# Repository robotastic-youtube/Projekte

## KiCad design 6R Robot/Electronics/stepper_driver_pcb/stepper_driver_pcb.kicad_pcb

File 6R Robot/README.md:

# Robotastic 6R-Robot & FOC Controller

This repository contains all the necessary resources for building and controlling a 6-axis robotic arm (6R-Robot), along with the custom electronics and firmware. The project relies on a hardware abstraction layer and Field-Oriented Control (FOC) for precise stepper motor operation.

## ⚠️ IMPORTANT SAFETY WARNING & DISCLAIMER ⚠️

This project involves building and operating a **6-axis robot** driven by stepper motors and custom electronics. Please strictly observe the following points before attempting to build or operate it:

* **Mechanical Hazard:** A robotic arm can move unpredictably, at high speeds, and with significant force—especially during programming, FOC parameter tuning, or due to unforeseen software bugs. Always maintain a safe distance during operation and **never** reach into the robot's workspace while it is powered on!
* **Electrical Hazard:** This system operates with voltages and high-current power supplies (e.g., 24V) that can cause fires, severe injuries, or the destruction of hardware if wired incorrectly, short-circuited, or overloaded. Adequate foundational knowledge of electronics is strictly required.
* **Not an Industrial Product:** This is an experimental DIY and educational project. It does not carry a CE mark and lacks the certified safety mechanisms (such as verified emergency stop chains or light curtains) found in commercial industrial robots.

**Use at Your Own Risk:**
Building, programming, and operating this robot is done **entirely at your own risk**. The author (Robotastic) assumes absolutely no liability for any personal injury, property damage, or financial loss resulting from the construction, use, or potential malfunction of this project.

## 1. Folder Structure

The project is organized into three main directories:

* **`Electronics/`**: Contains the **KiCad files** for the custom FOC PCB designed to drive the stepper motors.
* **`Code/`**: Contains the **Firmware** for the PCBs. This code is built using PlatformIO and implements hardware initialization, CAN-bus communication, and the FOC algorithm.
* **`3D-Files/`**: Contains the mechanical designs in **STEP format**.
    * Individual joints are provided as assemblies named `Joint1` through `Joint6`.
    * The file `6R-Robot Assembly` contains the complete, assembled robot model.

## 2. Documentation & Build Guide

For detailed videos on how to assemble the robot, explanations of the electronics, and the software, please visit the **Robotastic YouTube Channel**:

👉 [Robotastic YouTube Channel](https://www.youtube.com/channel/UCKuV_Eh0zMl3OSophDiDIqA)

## 3. Current Project Status (Hardware)

Please note that this project is currently a **Work in Progress (WIP)**.
* There is currently **no official Bill of Materials (BOM)** or detailed guide available.
* However, the robot can still be built, as the necessary components can be inferred from the provided documentation, PCB designs, and 3D models.

## 4. Software Status

The firmware provided in the `Code/` folder is designed for the direct low-level control of the motor drivers:
* **Currently Implemented**: Low-level drivers, FOC logic, CAN communication, and simple motion commands (Position, Velocity, Torque, Trajectory points).
* **Not Yet Implemented**: There is currently **no high-level software** for path planning (such as Inverse Kinematics or full-arm trajectory generation) or a graphical user interface (GUI) to control the robot as a complete system.

## 5. Getting Started (PlatformIO)

This project is built using **PlatformIO**, which is the recommended development environment.

### How to load the project:
1. **Install VS Code:** Download and install Visual Studio Code.
2. **Install PlatformIO:** Search for the "PlatformIO IDE" extension in the VS Code marketplace and install it.
3. **Open Project:**
   - Clone this repository or download the source code.
   - In PlatformIO Home, click on "Open Project" and select the folder containing `platformio.ini`.
4. **Build & Upload:**
   - Connect your STM32 board via USB (ensure you have the correct programmer, e.g., ST-Link).
   - Use the PlatformIO toolbar (bottom bar) to click the **Build** (Checkmark) and then **Upload** (Arrow) icons.

## License

This software, hardware design, and mechanical design are provided for **educational and personal use only**. 
**Commercial use is strictly prohibited** without prior written permission from the author. 

Please see the `LICENSE` file for the complete Robotastic Non-Commercial License terms.

*This project relies on the excellent SimpleFOC library, which is licensed under the MIT License.*

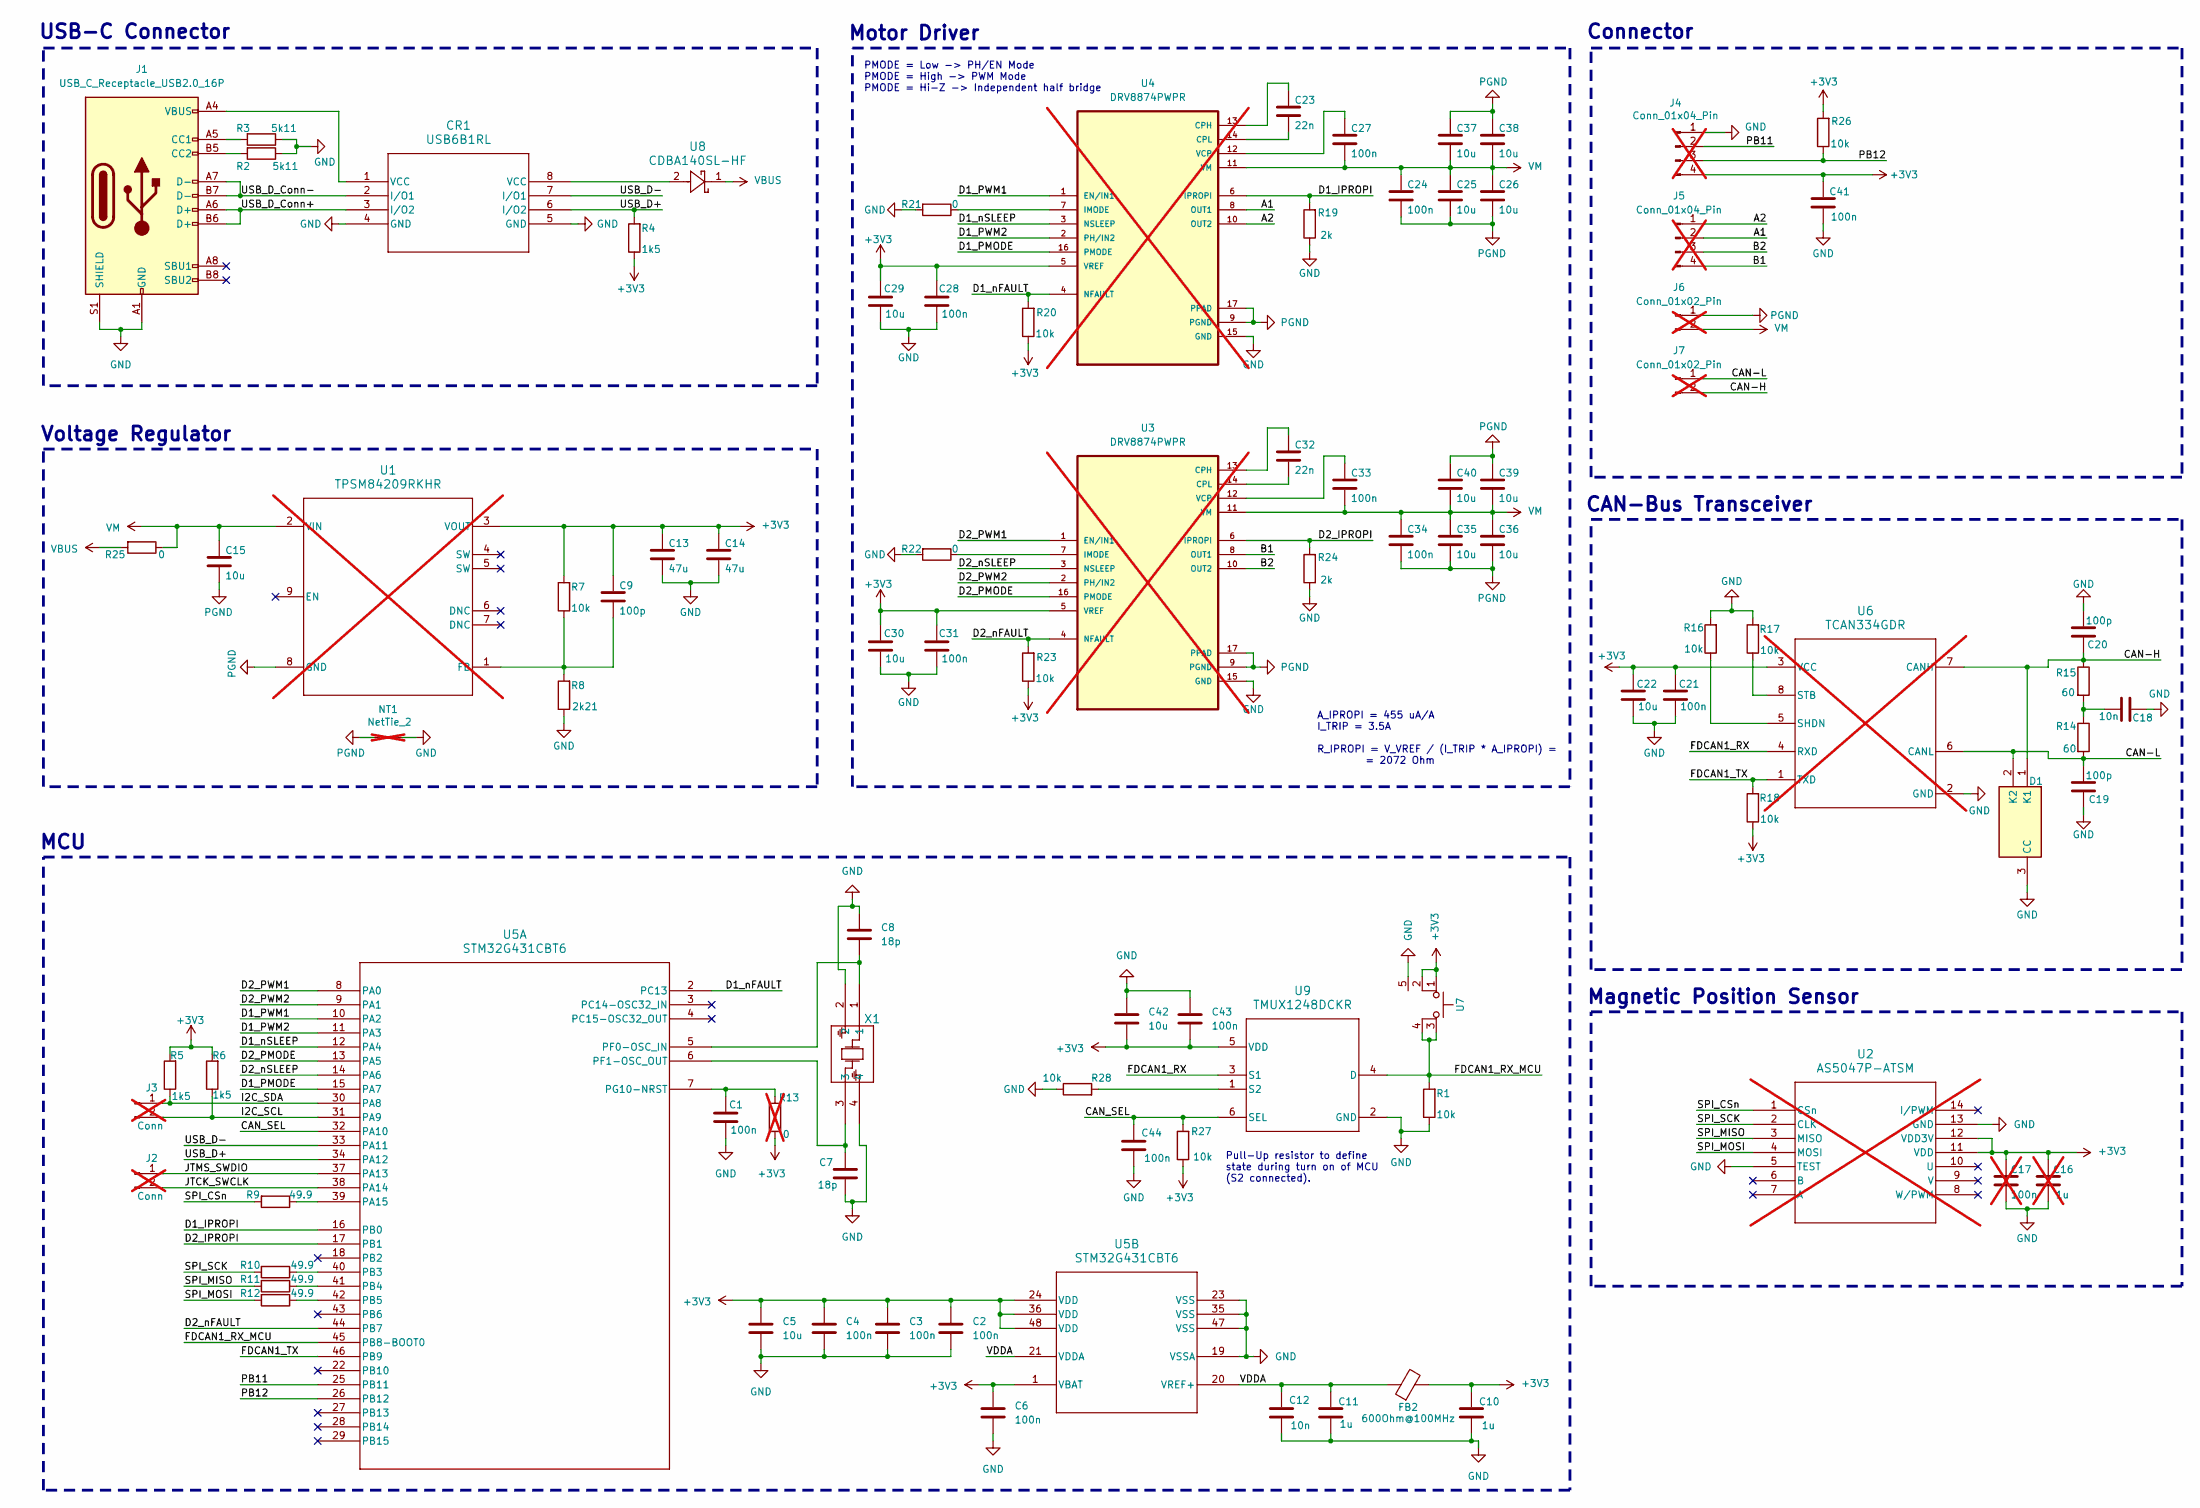
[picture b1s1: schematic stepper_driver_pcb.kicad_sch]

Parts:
C1, C2, C3, C4, C6, C21, C24, C27, C28, C31, C33, C34, C41, C43, C44: 100n; C_0603_1608Metric; LCSC C14663
C5, C22, C29, C30, C42: 10u; C_0603_1608Metric; LCSC C19702
C7, C8: 18p; C_0603_1608Metric; LCSC C1647
C9, C19, C20: 100p; C_0603_1608Metric; LCSC C14858
C10, C11: 1u; C_0603_1608Metric; LCSC C15849
C12, C18: 10n; C_0603_1608Metric; LCSC C57112
C13, C14: 47u; C_0805_2012Metric; LCSC C16780
C15: 10u; C_0805_2012Metric; LCSC C440198
C16: 1u; C_0603_1608Metric; LCSC C15849; not fitted
C17: 100n; C_0603_1608Metric; LCSC C14663; not fitted
C23, C32: 22n; C_0603_1608Metric; LCSC C21122
C25, C26, C35, C36, C37, C38, C39, C40: 10u; C_1206_3216Metric; LCSC C13585
CR1: USB6B1RL; SO-8_STM; LCSC C7419953
D1: PESD2CANFD24L-UX; SOT65P210X110-3N; Mouser Part Number 771-PESD2CANFD24L-UX
FB2: 600Ohm@100MHz; R_0603_1608Metric; LCSC C1002
J1: USB_C_Receptacle_USB2.0_16P; USB_C_Receptacle_G-Switch_GT-USB-7010ASV; LCSC C2988369
J2, J3: Conn; PinHeader_1x02_P2.54mm_Vertical; not fitted
J4: Conn_01x04_Pin; PinHeader_1x04_P2.54mm_Vertical; not fitted
J5: Conn_01x04_Pin; JST_XH_B4B-XH-AM_1x04_P2.50mm_Vertical; LCSC C5368777; not fitted
J6, J7: Conn_01x02_Pin; TerminalBlock_4Ucon_1x02_P3.50mm_Horizontal; not fitted
NT1: NetTie_2; NetTie-2_THT_Pad0.3mm; not fitted
R1, R7, R16, R17, R18, R20, R23, R26, R27, R28: 10k; R_0603_1608Metric; LCSC C25804
R2, R3: 5k11; R_0603_1608Metric; LCSC C23186
R4, R5, R6: 1k5; R_0603_1608Metric; LCSC C22843
R8: 2k21; R_0603_1608Metric; LCSC C4190
R9, R10, R11, R12: 49.9; R_0603_1608Metric; LCSC C23185
R13: 0; R_0603_1608Metric; LCSC C21189; not fitted
R14, R15: 60; R_0603_1608Metric; LCSC C2933247
R19, R24: 2k; R_0603_1608Metric; LCSC C22975
R21, R22, R25: 0; R_0603_1608Metric; LCSC C21189
U1: TPSM84209RKHR; RKH0009A; LCSC C2878926; not fitted
U2: AS5047P-ATSM; TSSOP14_OSM; LCSC C962063; not fitted
U3, U4: DRV8874PWPR; SOP65P640X120-17N; LCSC C1855818; not fitted
U5: STM32G431CBT6; LQFP48-7x7mm; LCSC C529355
U6: TCAN334GDR; D0008A_L; LCSC C189939; not fitted
U7: YTS-A007; LCSC C967770
U8: CDBA140SL-HF; CDBA-HF; LCSC C3012747
U9: TMUX1248DCKR; DCK0006A-IPC_C; LCSC C3656915
X1: ABM3B-8.000MHZ-B2-T; ABM3B_ABR; LCSC C83312

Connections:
+3V3: C2.1, C3.1, C4.1, C5.1, C6.1, C9.1, C10.1, C13.1, C14.1, C16.1, C17.1, C21.1, C22.1, C28.1, C29.1, C30.1, C31.1, C41.1, C42.2, C43.2, FB2.2, J4.4, R4.1, R5.2, R6.2, R7.2, R13.2, R18.1, R20.1, R23.1, R26.2, R27.1, U1.3 (VOUT), U2.11 (VDD), U2.12 (VDD3V), U3.5 (VREF), U4.5 (VREF), U5.1 (VBAT), U5.24 (VDD), U5.36 (VDD), U5.48 (VDD), U6.3 (VCC), U7.1, U7.2, U9.5 (VDD)
/A1: J5.2, U4.8 (OUT1)
/A2: J5.1, U4.10 (OUT2)
/B1: J5.4, U3.8 (OUT1)
/B2: J5.3, U3.10 (OUT2)
/CAN-H: C20.1, D1.1 (K1), J7.2, R15.1, U6.7 (CANH)
/CAN-L: C19.1, D1.2 (K2), J7.1, R14.2, U6.6 (CANL)
/CAN_SEL: C44.2, R27.2, U5.32 (PA10), U9.6 (SEL)
/D1_IPROPI: R19.2, U4.6 (IPROPI), U5.16 (PB0)
/D1_PMODE: U4.16 (PMODE), U5.15 (PA7)
/D1_PWM1: U4.1 (EN/IN1), U5.10 (PA2)
/D1_PWM2: U4.2 (PH/IN2), U5.11 (PA3)
/D1_nFAULT: R20.2, U4.4 (NFAULT), U5.2 (PC13)
/D1_nSLEEP: U4.3 (NSLEEP), U5.12 (PA4)
/D2_IPROPI: R24.2, U3.6 (IPROPI), U5.17 (PB1)
/D2_PMODE: U3.16 (PMODE), U5.13 (PA5)
/D2_PWM1: U3.1 (EN/IN1), U5.8 (PA0)
/D2_PWM2: U3.2 (PH/IN2), U5.9 (PA1)
/D2_nFAULT: R23.2, U3.4 (NFAULT), U5.44 (PB7)
/D2_nSLEEP: U3.3 (NSLEEP), U5.14 (PA6)
/FDCAN1_RX: U6.4 (RXD), U9.3 (S1)
/FDCAN1_RX_MCU: R1.2, U5.45 (PB8-BOOT0), U7.3, U7.4, U9.4 (D)
/FDCAN1_TX: R18.2, U5.46 (PB9), U6.1 (TXD)
/I2C_SCL: J3.2, R6.1, U5.31 (PA9)
/I2C_SDA: J3.1, R5.1, U5.30 (PA8)
/JTCK_SWCLK: J2.2, U5.38 (PA14)
/JTMS_SWDIO: J2.1, U5.37 (PA13)
/PB11: J4.2, U5.25 (PB11)
/PB12: J4.3, R26.1, U5.26 (PB12)
/SPI_CSn: R9.2, U2.1 (CSn)
/SPI_MISO: R11.2, U2.3 (MISO)
/SPI_MOSI: R12.2, U2.4 (MOSI)
/SPI_SCK: R10.2, U2.2 (CLK)
/USB_D+: CR1.6 (I/O2), R4.2, U5.34 (PA12)
/USB_D-: CR1.7 (I/O1), U5.33 (PA11)
/USB_D_Conn+: CR1.3 (I/O2), J1.A6 (D+), J1.B6 (D+)
/USB_D_Conn-: CR1.2 (I/O1), J1.A7 (D-), J1.B7 (D-)
/VDDA: C11.1, C12.1, FB2.1, U5.20 (VREF+), U5.21 (VDDA)
GND: C1.2, C2.2, C3.2, C4.2, C5.2, C6.2, C7.2, C8.1, C10.2, C11.2, C12.2, C13.2, C14.2, C16.2, C17.2, C18.1, C19.2, C20.2, C21.2, C22.2, C28.2, C29.2, C30.2, C31.2, C41.2, C42.1, C43.1, C44.1, CR1.4 (GND), CR1.5 (GND), D1.3 (CC), J1.A1 (GND), J1.A12 (GND), J1.B1 (GND), J1.B12 (GND), J1.S1 (SHIELD), J4.1, NT1.2, R1.1, R2.1, R3.1, R8.1, R16.2, R17.2, R19.1, R21.2, R22.2, R24.1, R28.1, U2.5 (TEST), U2.13 (GND), U3.15 (GND), U4.15 (GND), U5.19 (VSSA), U5.23 (VSS), U5.35 (VSS), U5.47 (VSS), U6.2 (GND), U7.5, U9.2 (GND), X1.2, X1.4
unnamed: C18.2, R14.1, R15.2
unnamed: CR1.1 (VCC), J1.A4 (VBUS), J1.A9 (VBUS), J1.B4 (VBUS), J1.B9 (VBUS)
unnamed: CR1.8 (VCC), U8.2
unnamed: J1.A5 (CC1), R3.2
unnamed: J1.B5 (CC2), R2.2
unnamed: C9.2, R7.1, R8.2, U1.1 (FB)
unnamed: C32.1, U3.13 (CPH)
unnamed: C32.2, U3.14 (CPL)
unnamed: R22.1, U3.7 (IMODE)
unnamed: C33.1, U3.12 (VCP)
unnamed: C23.1, U4.13 (CPH)
unnamed: C23.2, U4.14 (CPL)
unnamed: R21.1, U4.7 (IMODE)
unnamed: C27.1, U4.12 (VCP)
unnamed: R9.1, U5.39 (PA15)
unnamed: R10.1, U5.40 (PB3)
unnamed: R11.1, U5.41 (PB4)
unnamed: R12.1, U5.42 (PB5)
unnamed: C8.2, U5.5 (PF0-OSC_IN), X1.1
unnamed: C7.1, U5.6 (PF1-OSC_OUT), X1.3
unnamed: C1.1, R13.1, U5.7 (PG10-NRST)
unnamed: R16.1, U6.5 (SHDN)
unnamed: R17.1, U6.8 (STB)
unnamed: R28.2, U9.1 (S2)
PGND: C15.2, C24.2, C25.2, C26.2, C34.2, C35.2, C36.2, C37.1, C38.1, C39.1, C40.1, J6.1, NT1.1, U1.8 (GND), U3.9 (PGND), U3.17 (PPAD), U4.9 (PGND), U4.17 (PPAD)
VBUS: R25.2, U8.1
VM: C15.1, C24.1, C25.1, C26.1, C27.2, C33.2, C34.1, C35.1, C36.1, C37.2, C38.2, C39.2, C40.2, J6.2, R25.1, U1.2 (VIN), U3.11 (VM), U4.11 (VM)

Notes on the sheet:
PMODE = Low -> PH/EN Mode PMODE = High -> PWM Mode PMODE = Hi-Z -> Independent half bridge
MCU
Magnetic Position Sensor
Connector
A_IPROPI = 455 uA/A I_TRIP = 3.5A R_IPROPI = V_VREF / (I_TRIP * A_IPROPI) = = 2072 Ohm
USB-C Connector
CAN-Bus Transceiver
Pull-Up resistor to define state during turn on of MCU (S2 connected).
Motor Driver
Voltage Regulator

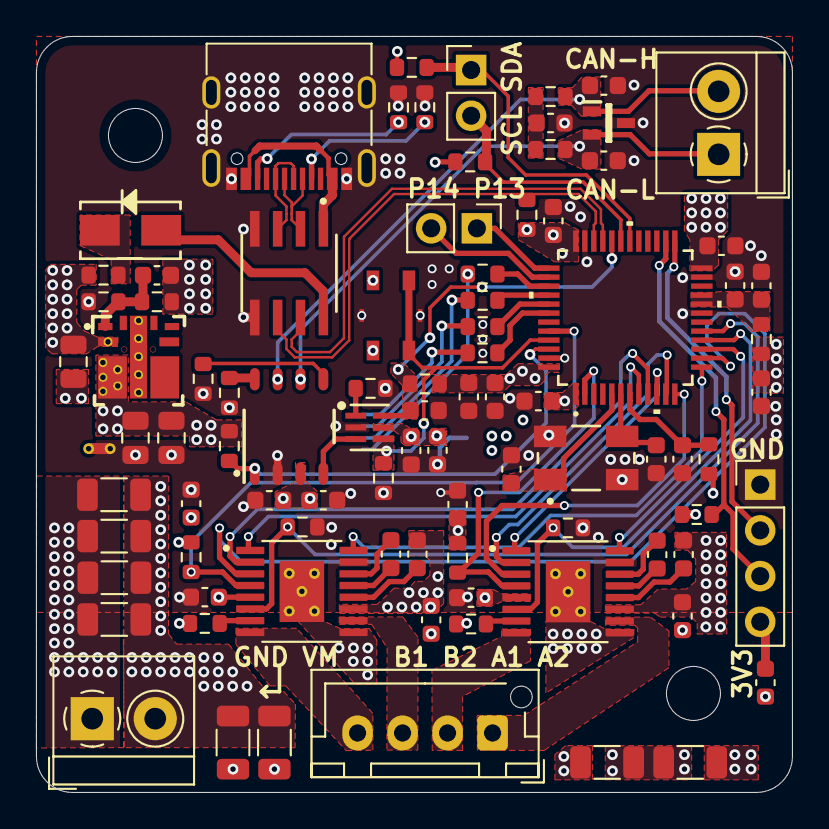
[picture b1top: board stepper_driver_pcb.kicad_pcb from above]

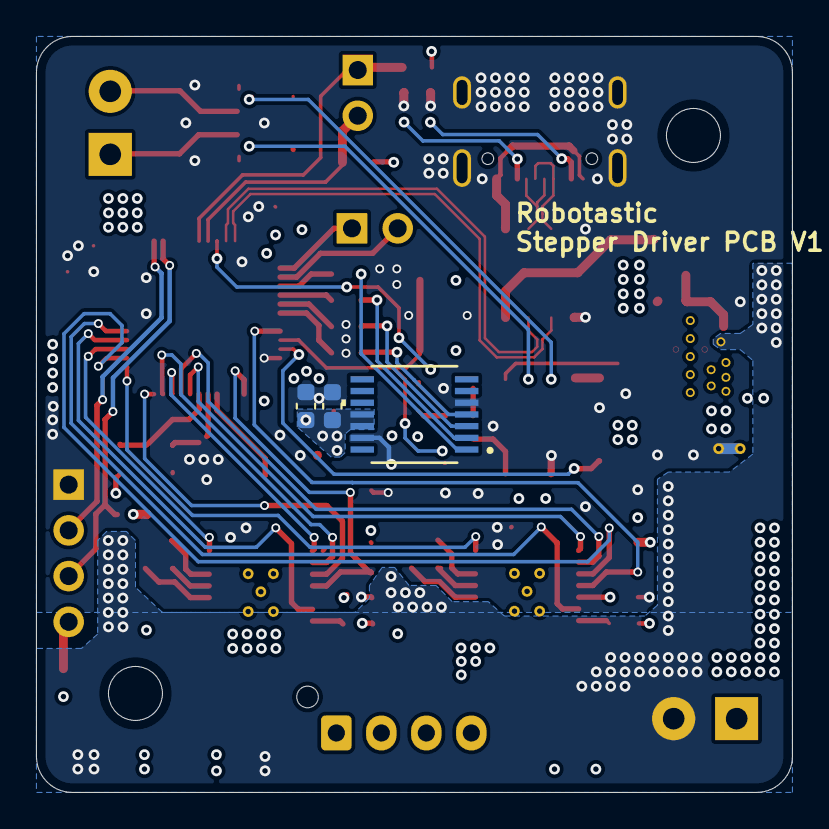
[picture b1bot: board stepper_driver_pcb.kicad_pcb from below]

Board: 4 copper layers, 42.0 x 42.0 mm, 93 parts (3 on the bottom side), 66 nets.

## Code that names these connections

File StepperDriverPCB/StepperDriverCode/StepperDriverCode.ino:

// Include STM32 HAL headers for hardware abstraction
#include "stm32g4xx_hal.h"
#include "stm32g4xx_hal_rcc.h"

// USB CDC (virtual COM port) interface
#include "usbd_cdc_if.h"
#include "usbd_cdc.h"

// SimpleFOC library and drivers
#include <SimpleFOC.h>
#include <SPI.h>
#include <Wire.h>
#include "SimpleFOCDrivers.h"
#include "encoders/as5047/MagneticSensorAS5047.h"

// Redefine external clock source to 8 MHz (ceramic resonator)
#undef HSE_VALUE
#define HSE_VALUE ((uint32_t)8000000)  

// Motor phase pin configuration
#define PHASE_A_PIN1 PA3
#define PHASE_A_PIN2 PA2
#define PHASE_B_PIN1 PA1
#define PHASE_B_PIN2 PA0
#define ENABLE_A_PIN PA4
#define ENABLE_B_PIN PA6

// AS5047 encoder SPI pins
#define AS5047_CS PA15 
#define AS5047_MOSI PB5 
#define AS5047_MISO PB4 
#define AS5047_SCK PB3 

// I2C address definition
#define I2C_ADDRESS 0x42

// Peripheral handle declarations
ADC_HandleTypeDef hadc1;
PCD_HandleTypeDef hpcd_USB_FS;
I2C_HandleTypeDef hi2c2;

// SPI instance for AS5047
SPIClass SPI3Instance(AS5047_MOSI, AS5047_MISO, AS5047_SCK);

// Motor and driver setup
StepperMotor motor = StepperMotor(50); // Stepper motor with 50 pole pairs
StepperDriver4PWM driver = StepperDriver4PWM(PHASE_A_PIN1, PHASE_A_PIN2, PHASE_B_PIN1, PHASE_B_PIN2, ENABLE_A_PIN, ENABLE_B_PIN);
MagneticSensorAS5047 sensor = MagneticSensorAS5047(AS5047_CS, 1);
LowsideCurrentSense current_sense = LowsideCurrentSense(910.0, PB0, PB1); // 910 mV/A, ADC pins PB0 and PB1

// Forward declarations for system configuration
void SystemClock_Config(void);
static void MX_GPIO_Init(void);
static void MX_USB_PCD_Init(void);
static void MX_I2C2_Init(void);
static void MX_ADC1_Init(void);

// Timer variables for control loop
unsigned long previousMillis = 0;
unsigned long previousPreviousMillis = 0;
const unsigned long interval = 10;

float motor_target = 0.0;

void setup() {
  HAL_Init();                      // Initialize the HAL library
  SystemClock_Config();           // Configure system clock
  MX_GPIO_Init();                 // Initialize GPIO
  MX_USB_PCD_Init();             // Initialize USB peripheral
  MX_ADC1_Init();                 // Initialize ADC1

  // Configure I2C pins and initialize
  Wire.setSCL(PA9);
  Wire.setSDA(PA8);
  Wire.begin();

  // Configure H-bridge mode pins
  pinMode(PA7, INPUT); // Set H-bridge 1 mode (independent half-bridge, high-Z)
  pinMode(PA5, INPUT); // Set H-bridge 2 mode
  pinMode(PB11, OUTPUT); // General purpose output pin

  sensor.init(&SPI3Instance); // Initialize magnetic sensor

  // Motor driver settings
  driver.voltage_power_supply = 20;
  driver.voltage_limit = 20;
  driver.pwm_frequency = 30000;
  driver.init();  // Initialize motor driver

  // Link and initialize current sensing
  current_sense.linkDriver(&driver);
  current_sense.init();

  // Connect components to motor object
  motor.linkSensor(&sensor);
  motor.linkDriver(&driver);
  motor.linkCurrentSense(&current_sense);

  // Motor control settings
  motor.voltage_limit = driver.voltage_limit / 2;
  motor.voltage_sensor_align = 5;

  // Select motor control modes
  // motor.controller = MotionControlType::velocity;
  motor.controller = MotionControlType::angle;
  // motor.torque_controller = TorqueControlType::voltage;
  // motor.torque_controller = TorqueControlType::foc_current;
  motor.foc_modulation = FOCModulationType::SinePWM; // SinePWM modulation
  // motor.controller = MotionControlType::torque;

  // Current control PID parameters
  motor.PID_current_q.P = 5;
  motor.PID_current_q.I = 1000;
  motor.PID_current_d.P = 5;
  motor.PID_current_d.I = 1000;
  motor.LPF_current_q.Tf = 0.002f;
  motor.LPF_current_d.Tf = 0.002f;
  motor.current_limit = 2;

  // Velocity control PID parameters
  motor.PID_velocity.P = 0.5;
  motor.PID_velocity.I = 10;
  motor.PID_velocity.D = 0;
  motor.LPF_velocity.Tf = 0.05f;

  // Angle (position) control PID parameters
  motor.P_angle.P = 20;
  motor.P_angle.I = 5;
  motor.P_angle.D = 0.001;
  motor.P_angle.output_ramp = 10000;
  motor.velocity_limit = 30;

  // Initialize motor and FOC algorithm
  motor.init();
  motor.initFOC();

  motor_target = 2; // Set target angle
}

void loop() {
  motor.loopFOC(); // Execute FOC algorithm

  unsigned long currentMillis = millis();

  // Run motor control loop every 10 ms
  if (currentMillis - previousMillis >= interval){
    motor.move(motor_target); // Move to target position
    previousMillis = currentMillis;
  }
}

// System clock configuration
void SystemClock_Config(void)
{
  RCC_OscInitTypeDef RCC_OscInitStruct = {0};
  RCC_ClkInitTypeDef RCC_ClkInitStruct = {0};

  HAL_PWREx_ControlVoltageScaling(PWR_REGULATOR_VOLTAGE_SCALE1);

  // Configure internal oscillators and PLL
  RCC_OscInitStruct.OscillatorType = RCC_OSCILLATORTYPE_HSI|RCC_OSCILLATORTYPE_HSI48;
  RCC_OscInitStruct.HSIState = RCC_HSI_ON;
  RCC_OscInitStruct.HSICalibrationValue = RCC_HSICALIBRATION_DEFAULT;
  RCC_OscInitStruct.HSI48State = RCC_HSI48_ON;
  RCC_OscInitStruct.PLL.PLLState = RCC_PLL_ON;
  RCC_OscInitStruct.PLL.PLLSource = RCC_PLLSOURCE_HSI;
  RCC_OscInitStruct.PLL.PLLM = RCC_PLLM_DIV1;
  RCC_OscInitStruct.PLL.PLLN = 18;
  RCC_OscInitStruct.PLL.PLLP = RCC_PLLP_DIV2;
  RCC_OscInitStruct.PLL.PLLQ = RCC_PLLQ_DIV6;
  RCC_OscInitStruct.PLL.PLLR = RCC_PLLR_DIV2;

  if (HAL_RCC_OscConfig(&RCC_OscInitStruct) != HAL_OK)
  {
    Error_Handler();
  }

  // Configure system clocks
  RCC_ClkInitStruct.ClockType = RCC_CLOCKTYPE_HCLK|RCC_CLOCKTYPE_SYSCLK
                              |RCC_CLOCKTYPE_PCLK1|RCC_CLOCKTYPE_PCLK2;
  RCC_ClkInitStruct.SYSCLKSource = RCC_SYSCLKSOURCE_PLLCLK;
  RCC_ClkInitStruct.AHBCLKDivider = RCC_SYSCLK_DIV1;
  RCC_ClkInitStruct.APB1CLKDivider = RCC_HCLK_DIV4;
  RCC_ClkInitStruct.APB2CLKDivider = RCC_HCLK_DIV4;

  if (HAL_RCC_ClockConfig(&RCC_ClkInitStruct, FLASH_LATENCY_4) != HAL_OK)
  {
    Error_Handler();
  }
}

// USB peripheral initialization
static void MX_USB_PCD_Init(void)
{
  hpcd_USB_FS.Instance = USB;
  hpcd_USB_FS.Init.dev_endpoints = 8;
  hpcd_USB_FS.Init.speed = PCD_SPEED_FULL;
  hpcd_USB_FS.Init.phy_itface = PCD_PHY_EMBEDDED;
  hpcd_USB_FS.Init.Sof_enable = DISABLE;
  hpcd_USB_FS.Init.low_power_enable = DISABLE;
  hpcd_USB_FS.Init.lpm_enable = DISABLE;
  hpcd_USB_FS.Init.battery_charging_enable = DISABLE;

  if (HAL_PCD_Init(&hpcd_USB_FS) != HAL_OK)
  {
    // Error_Handler();
  }

  HAL_PCD_Start(&hpcd_USB_FS); // Start USB device
}

// GPIO initialization
static void MX_GPIO_Init(void)
{
  __HAL_RCC_GPIOF_CLK_ENABLE();
  __HAL_RCC_GPIOB_CLK_ENABLE();
  __HAL_RCC_GPIOA_CLK_ENABLE();
}

// ADC1 initialization
static void MX_ADC1_Init(void)
{
  ADC_MultiModeTypeDef multimode = {0};
  ADC_ChannelConfTypeDef sConfig = {0};

  hadc1.Instance = ADC1;
  hadc1.Init.ClockPrescaler = ADC_CLOCK_SYNC_PCLK_DIV2;
  hadc1.Init.Resolution = ADC_RESOLUTION_12B;
  hadc1.Init.DataAlign = ADC_DATAALIGN_RIGHT;
  hadc1.Init.GainCompensation = 0;
  hadc1.Init.ScanConvMode = ADC_SCAN_DISABLE;
  hadc1.Init.EOCSelection = ADC_EOC_SINGLE_CONV;
  hadc1.Init.LowPowerAutoWait = DISABLE;
  hadc1.Init.ContinuousConvMode = DISABLE;
  hadc1.Init.NbrOfConversion = 1;
  hadc1.Init.DiscontinuousConvMode = DISABLE;
  hadc1.Init.ExternalTrigConv = ADC_SOFTWARE_START;
  hadc1.Init.ExternalTrigConvEdge = ADC_EXTERNALTRIGCONVEDGE_NONE;
  hadc1.Init.DMAContinuousRequests = DISABLE;
  hadc1.Init.Overrun = ADC_OVR_DATA_PRESERVED;
  hadc1.Init.OversamplingMode = DISABLE;

  if (HAL_ADC_Init(&hadc1) != HAL_OK)
  {
    // Error_Handler();
  }

  multimode.Mode = ADC_MODE_INDEPENDENT;
  if (HAL_ADCEx_MultiModeConfigChannel(&hadc1, &multimode) != HAL_OK)
  {
    // Error_Handler();
  }

  // Configure ADC channel
  sConfig.Channel = ADC_CHANNEL_15;
  sConfig.Rank = ADC_REGULAR_RANK_1;
  sConfig.SamplingTime = ADC_SAMPLETIME_2CYCLES_5;
  sConfig.SingleDiff = ADC_SINGLE_ENDED;
  sConfig.OffsetNumber = ADC_OFFSET_NONE;
  sConfig.Offset = 0;

  if (HAL_ADC_ConfigChannel(&hadc1, &sConfig) != HAL_OK)
  {
    // Error_Handler();
  }
}

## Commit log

2023-11-30 add arduino program for transmitter
2023-12-14 add mecanum wheel files and python script
2023-12-14 renamed file
2024-04-12 added selfbalancing robot
2024-05-05 added pid controller library
2024-05-16 added receiver code
2024-06-02 harmonic drive files added
2025-05-25 added stepper driver pcb files
2025-05-25 added README with information about current hardware problem
2025-09-08 6R-Robot CAD-Files
2026-04-12 added step-, pcb-, and KiCad-files for 6R-Robot; included FOC PCB files in 6R-Robot folder
